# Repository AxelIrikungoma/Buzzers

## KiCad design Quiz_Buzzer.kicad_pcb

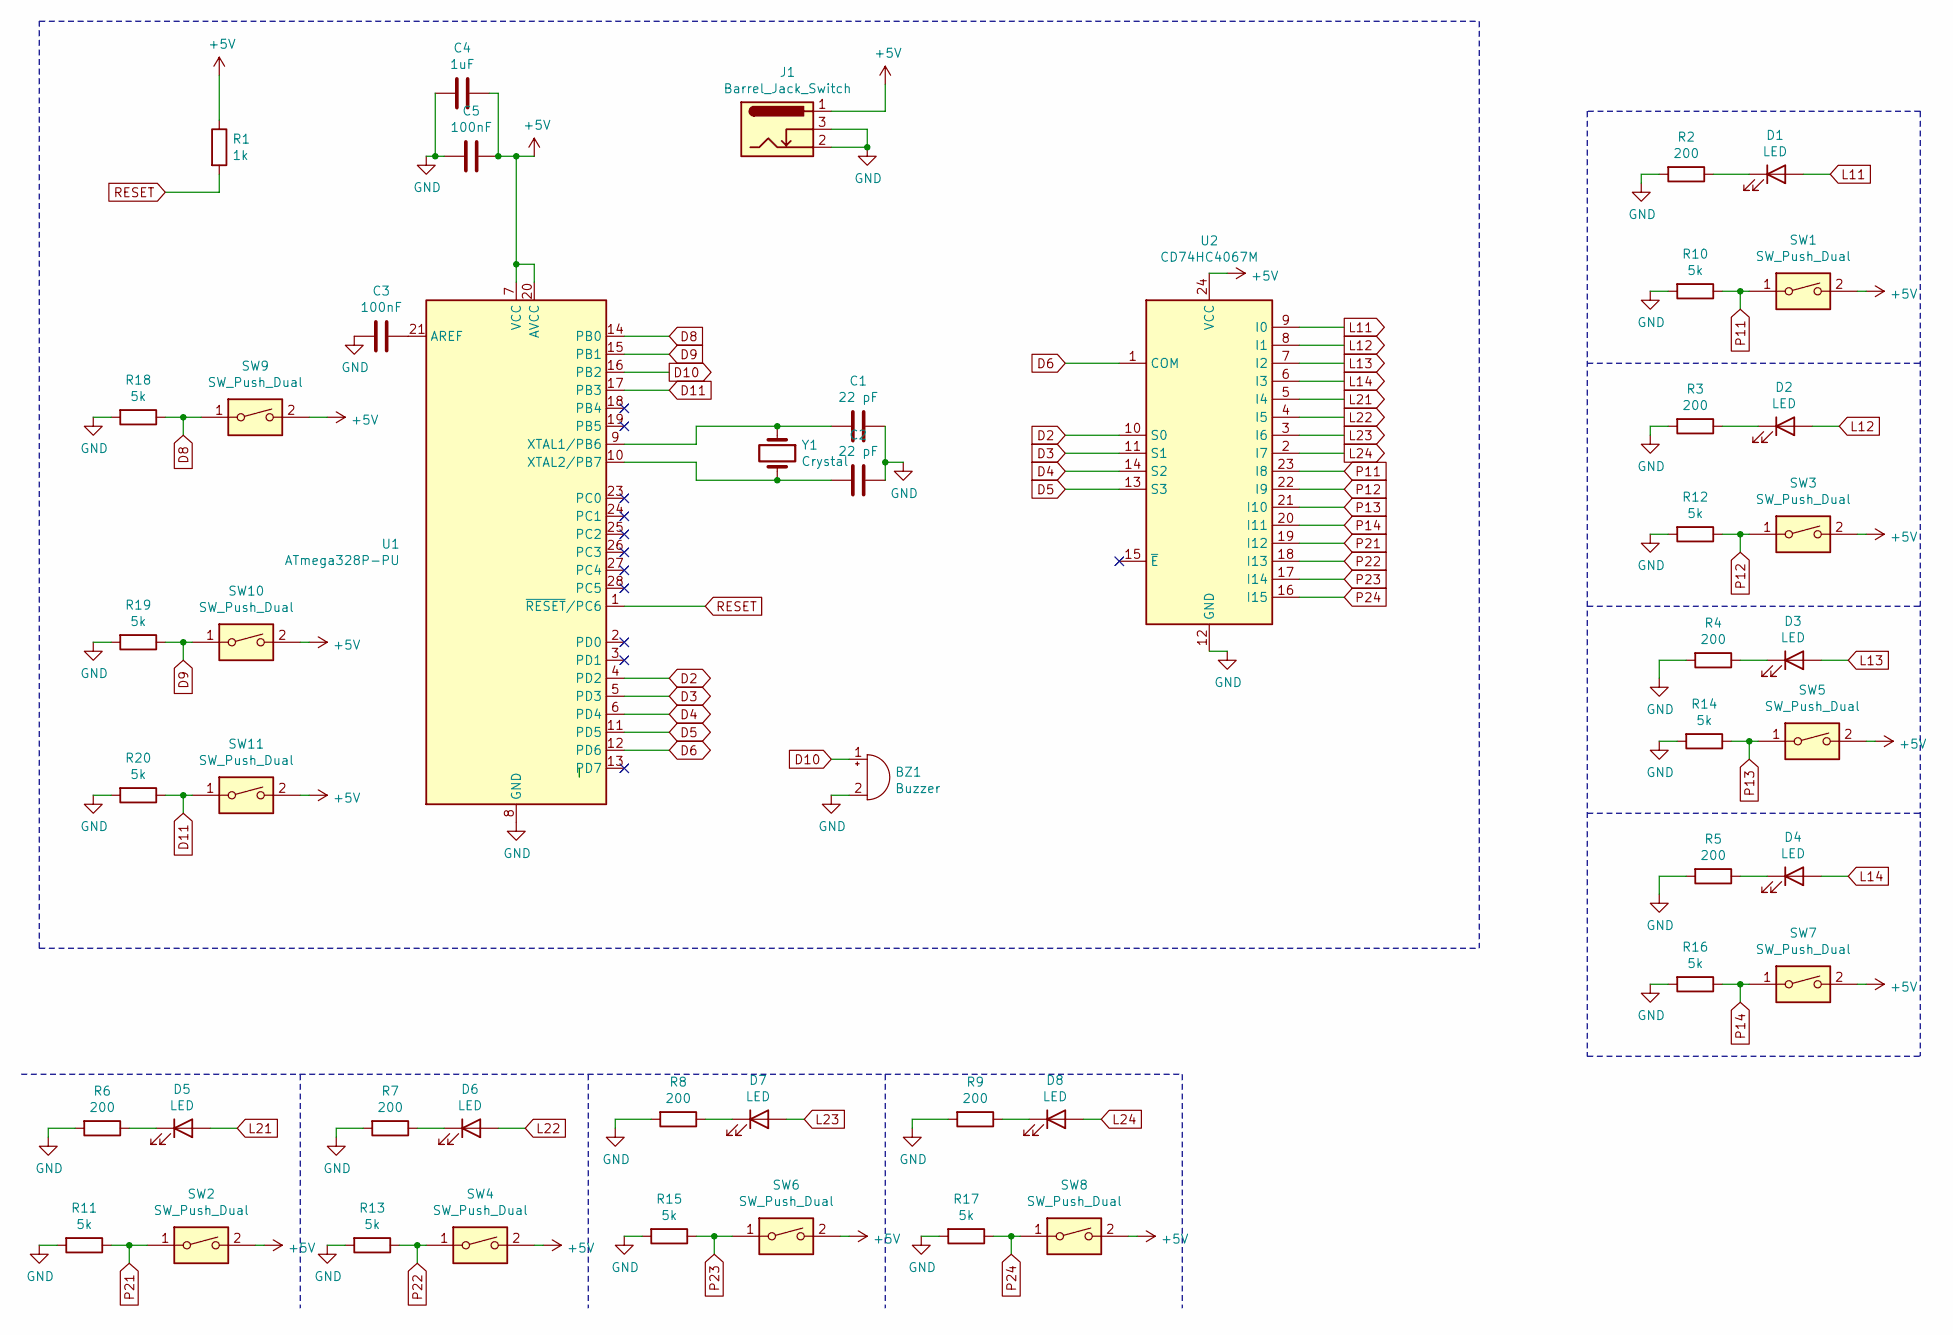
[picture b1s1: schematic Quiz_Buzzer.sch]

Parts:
BZ1: Buzzer; Buzzer_12x9.5RM7.6
C1, C2: 22 pF; C_Axial_L3.8mm_D2.6mm_P7.50mm_Horizontal
C3, C5: 100nF; C_Axial_L3.8mm_D2.6mm_P7.50mm_Horizontal
C4: 1uF; C_Axial_L3.8mm_D2.6mm_P7.50mm_Horizontal
D1, D2, D3, D4, D5, D6, D7, D8: LED; LED_D3.0mm
J1: Barrel_Jack_Switch; BarrelJack_CLIFF_FC681465S_SMT_Horizontal
R1: 1k; R_Axial_DIN0309_L9.0mm_D3.2mm_P12.70mm_Horizontal
R2, R3, R4, R5, R6, R7, R8, R9: 200; R_Axial_DIN0309_L9.0mm_D3.2mm_P12.70mm_Horizontal
R10, R11, R12, R13, R14, R15, R16, R17, R18, R19, R20: 5k; R_Axial_DIN0309_L9.0mm_D3.2mm_P12.70mm_Horizontal
SW1, SW2, SW3, SW4, SW5, SW6, SW7, SW8, SW9, SW10, SW11: SW_Push_Dual; SW_PUSH_6mm
U1: ATmega328P-PU; DIP-28_W7.62mm
U2: CD74HC4067M; SOIC-24W_7.5x15.4mm_P1.27mm
Y1: Crystal; Crystal_HC49-4H_Vertical

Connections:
+5V: C4.1, C5.1, J1.1, R1.1, SW1.2, SW2.2, SW3.2, SW4.2, SW5.2, SW6.2, SW7.2, SW8.2, SW9.2, SW10.2, SW11.2, U1.7 (VCC), U1.20 (AVCC), U2.24 (VCC)
D2: U1.4 (PD2), U2.10 (S0)
D3: U1.5 (PD3), U2.11 (S1)
D4: U1.6 (PD4), U2.14 (S2)
D5: U1.11 (PD5), U2.13 (S3)
D6: U1.12 (PD6), U2.1 (COM)
D8: R18.1, SW9.1, U1.14 (PB0)
D9: R19.1, SW10.1, U1.15 (PB1)
D10: BZ1.1 (-), U1.16 (PB2)
D11: R20.1, SW11.1, U1.17 (PB3)
GND: BZ1.2 (+), C1.1, C2.2, C3.2, C4.2, C5.2, J1.2, J1.3, R2.2, R3.2, R4.2, R5.2, R6.2, R7.2, R8.2, R9.2, R10.2, R11.2, R12.2, R13.2, R14.2, R15.2, R16.2, R17.2, R18.2, R19.2, R20.2, U1.8 (GND), U1.22 (GND), U2.12 (GND)
L11: D1.2 (A), U2.9 (I0)
L12: D2.2 (A), U2.8 (I1)
L13: D3.2 (A), U2.7 (I2)
L14: D4.2 (A), U2.6 (I3)
L21: D5.2 (A), U2.5 (I4)
L22: D6.2 (A), U2.4 (I5)
L23: D7.2 (A), U2.3 (I6)
L24: D8.2 (A), U2.2 (I7)
unnamed: C1.2, U1.9 (XTAL1/PB6), Y1.1
unnamed: C2.1, U1.10 (XTAL2/PB7), Y1.2
unnamed: C3.1, U1.21 (AREF)
unnamed: D1.1 (K), R2.1
unnamed: D2.1 (K), R3.1
unnamed: D3.1 (K), R4.1
unnamed: D4.1 (K), R5.1
unnamed: D5.1 (K), R6.1
unnamed: D6.1 (K), R7.1
unnamed: D7.1 (K), R8.1
unnamed: D8.1 (K), R9.1
P11: R10.1, SW1.1, U2.23 (I8)
P12: R12.1, SW3.1, U2.22 (I9)
P13: R14.1, SW5.1, U2.21 (I10)
P14: R16.1, SW7.1, U2.20 (I11)
P21: R11.1, SW2.1, U2.19 (I12)
P22: R13.1, SW4.1, U2.18 (I13)
P23: R15.1, SW6.1, U2.17 (I14)
P24: R17.1, SW8.1, U2.16 (I15)
RESET: R1.2, U1.1 (~RESET~/PC6)

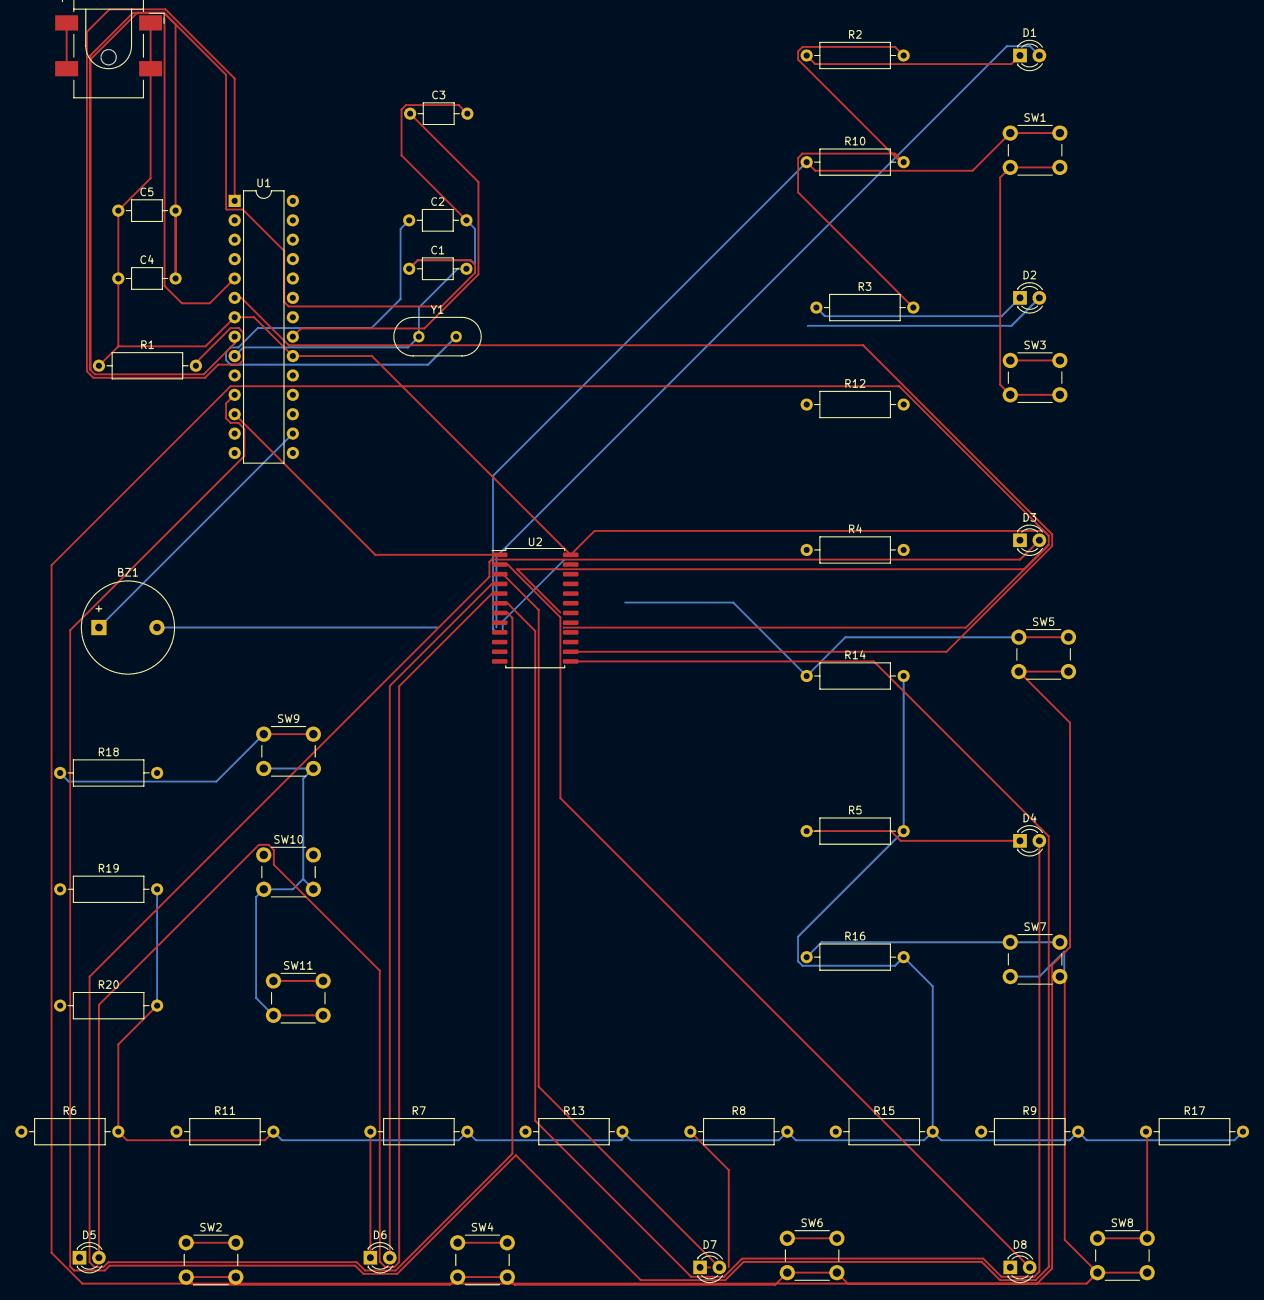
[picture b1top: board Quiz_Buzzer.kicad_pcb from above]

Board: 2 copper layers, 49 parts (0 on the bottom side), 39 nets.

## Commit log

2021-08-12 most recent version of quiz buzzers code
2021-08-16 adding schematic files
2021-08-16 adding all missing components in schematic file
2021-08-18 added pcb layout trial1
2021-09-07 Saving current work to make sure I don't lose it
